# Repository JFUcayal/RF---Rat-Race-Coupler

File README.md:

# 📡 Rat-Race Coupler Design @ 2.4 GHz

This repository presents the full development process of a **Rat-Race hybrid coupler** designed to operate at a **2.4 GHz** center frequency. The project focuses on applications in RF systems such as modulators, mixers, and wireless communication circuits.

<p align="center">
  
  &nbsp;&nbsp;
  
</p>

## 🧠 Project Objective

The goal of this project is to explore the design, simulation, and manufacturing of a Rat-Race coupler by:

- Splitting signals with a 180° phase shift and equal amplitude (3 dB split).
- Combining signals with preserved phase and power balance.
- Applying microstrip line theory and transmission line calculations.

## 🧰 Tools Used

- **MATLAB**: For simulating S-parameters and signal phase behavior.
- **KiCAD**: For PCB layout and physical design.

## 📈 Technical Highlights

- **Signal injected at Port 1**: Analysis of output at Ports 2 and 4, with Port 3 acting as the isolated port.
- **Performance comparison (real vs simulated)**:
  - S21 and S41 measured around -4.8 dB (simulated: -4 dB).
  - S11 showed increased reflection in real test (~ -3 dB vs -17 dB simulated).
- **Impedance matching**:
  - Outer lines: 50 Ω (≈ 3 mm width)
  - Upper line: 70.7 Ω (≈ 1.6 mm width)
    
## 🧾 Full Documentation

To learn more about the theory, simulations, physical implementation and analysis results:
👉 [📄 Open the full report](./TP_ERF_PG53914_rat_race_coupler.pdf)

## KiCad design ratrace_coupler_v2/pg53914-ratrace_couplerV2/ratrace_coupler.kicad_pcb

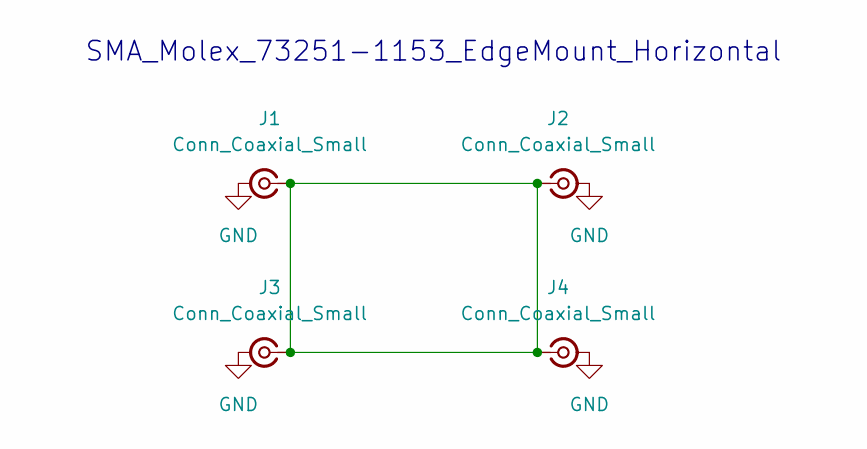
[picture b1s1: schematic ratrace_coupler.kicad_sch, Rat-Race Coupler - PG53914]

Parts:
J1, J2, J3, J4: Conn_Coaxial_Small; SMA_Molex_73251-1153_EdgeMount_Horizontal

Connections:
GND: J1.2 (Ext), J2.2 (Ext), J3.2 (Ext), J4.2 (Ext)
unnamed: J1.1 (In), J2.1 (In), J3.1 (In), J4.1 (In)

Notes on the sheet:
SMA_Molex_73251-1153_EdgeMount_Horizontal

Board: 2 copper layers, 4 parts (0 on the bottom side), 2 nets, no tracks yet.
